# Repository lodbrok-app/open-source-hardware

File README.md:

# open-source-hardware
Open-source components of the Lodbrok stack

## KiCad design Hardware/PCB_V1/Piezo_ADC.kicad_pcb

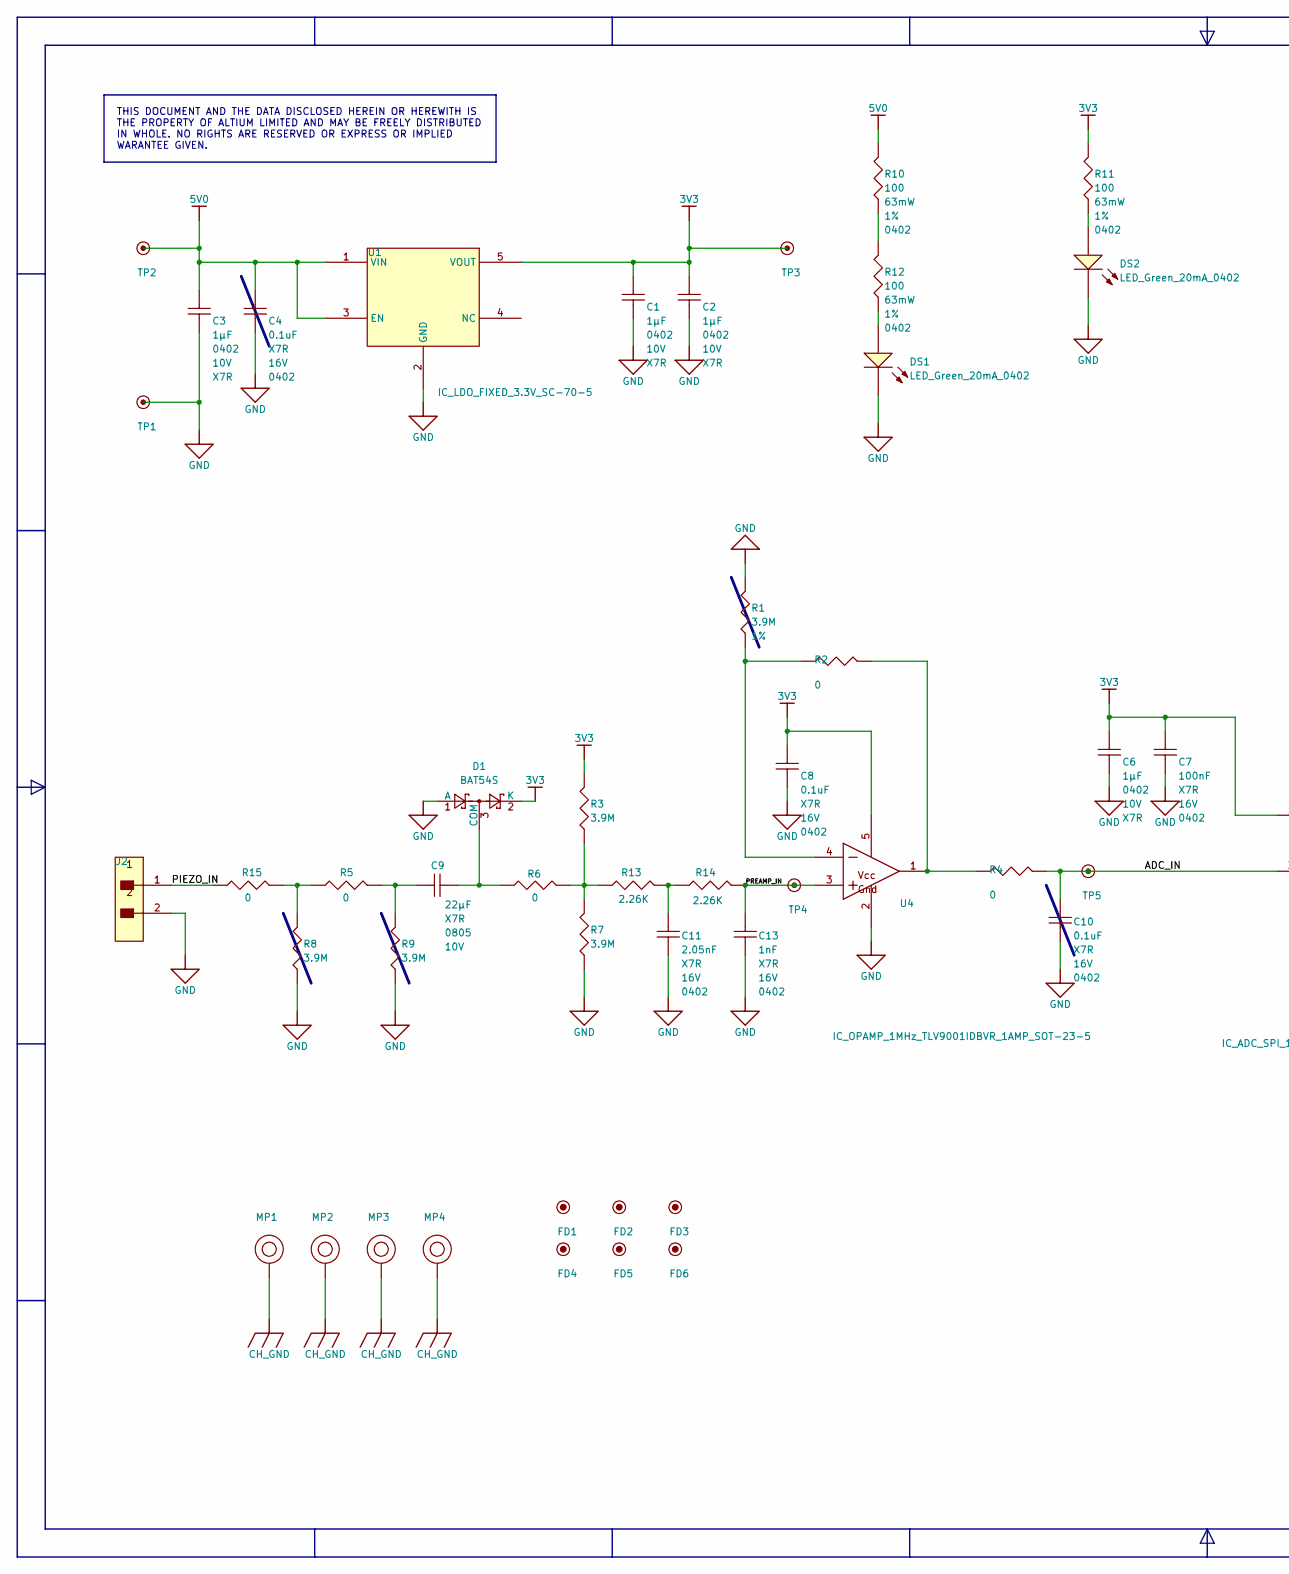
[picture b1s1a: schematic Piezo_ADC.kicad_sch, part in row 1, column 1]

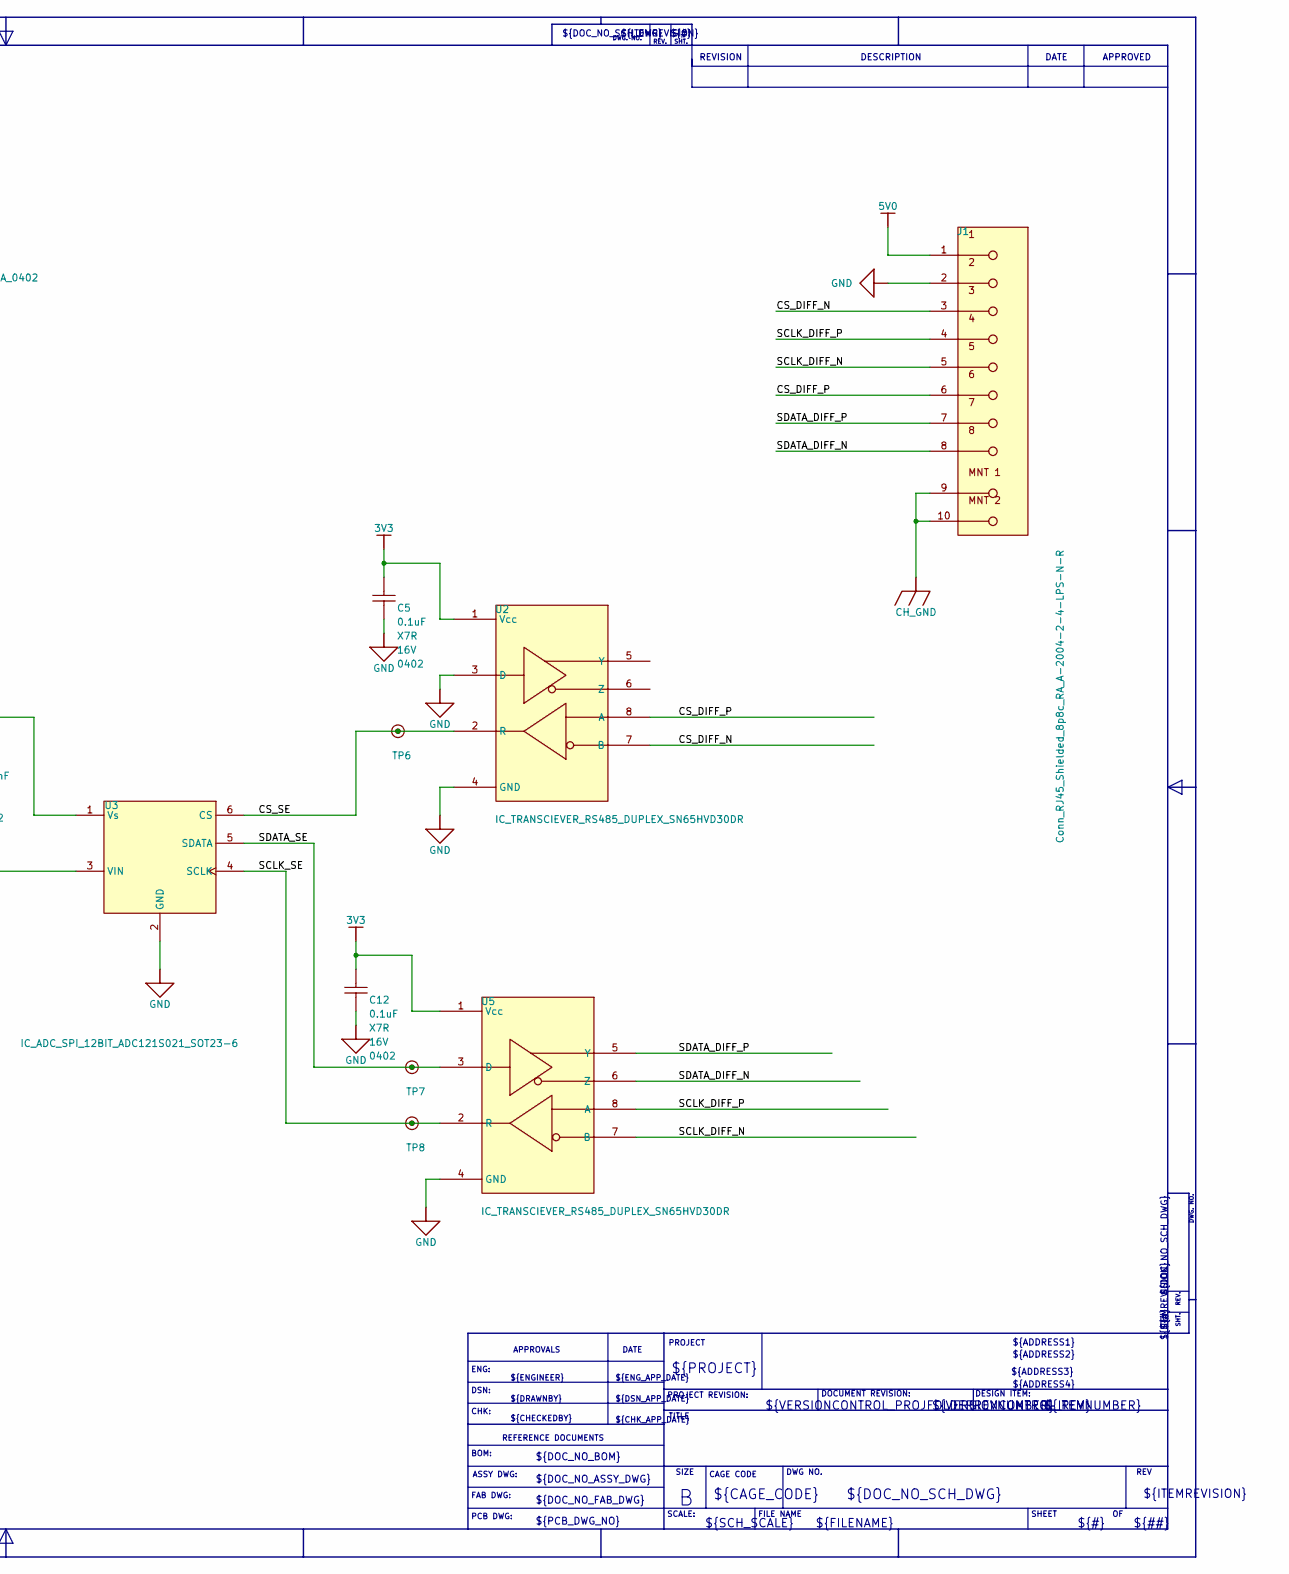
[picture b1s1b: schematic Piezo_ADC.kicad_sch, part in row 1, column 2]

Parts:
C1, C2, C3, C6: Cap_1uF_10%_10V_0402; CAP_0402_0.6mm_Height; VOLTAGE RATING 10V; TOLERANCE 10%
C4, C5, C7, C8, C10, C12: Cap_0.1uF_10%_16V_0402; CAP_0402_0.6mm_Height; TOLERANCE 10%; VOLTAGE RATING 16V
C9: Cap_22uF_20%_10V_0805; CAP_0805_1.45mm_Height; TOLERANCE 20%; VOLTAGE RATING 10V
C11: Cap_2.05nF_10%_16V_0402; CAP_0402_0.6mm_Height; TOLERANCE 10%; VOLTAGE RATING 16V
C13: Cap_1nF_10%_16V_0402; CAP_0402_0.6mm_Height; TOLERANCE 10%; VOLTAGE RATING 16V
D1: BAT54S; SOT-23
DS1, DS2: LED_Green_20mA_0402; LED_0402_Green_KA; FORWARD VOLTAGE 2.1V
FD1, FD2, FD3, FD4, FD5, FD6: FID1X2R
J1: Conn_RJ45_Shielded_8p8c_RA_A-2004-2-4-LPS-N-R; A-2004-2-4-LPS-N-R; VOLTAGE RATING 150V
J2: Conn_2Pos_3.96mm_1Row_TH_JST_B2PS-VH; JST_B2PS-VH-FP; VOLTAGE RATING 250V; MPN1 B2PS-VH
MP1, MP2, MP3, MP4: STAND_OFF_M3_2mm_NS_SMT; 9774020960
R1: Res_3M9_1%_63mW_0402; RES_0402; TOLERANCE 1%; VOLTAGE RATING 50V
R2, R4, R5, R6, R15: Res_0R0_1%_63mW_0402; RES_0402; VOLTAGE RATING 50V
R3, R7, R8, R9: Res_3M9_1%_63mW_0402; RES_0402; VOLTAGE RATING 50V
R10, R11, R12: Res_100R_1%_63mW_0402; RES_0402; TOLERANCE 1%; VOLTAGE RATING 50V
R13, R14: Res_2.26kR0_1%_63mW_0402; RES_0402; VOLTAGE RATING 50V
TP1, TP3, TP5, TP6, TP7, TP8: TPAD6R; Keystone 5001 TP
TP2, TP4: TPAD6R; TP06R
U1: IC_LDO_FIXED_3.3V_SC-70-5; SOT23-5; OUTPUT VOLTAGE 3.3V; DROPOUT VOLTAGE 310mV
U2, U5: IC_TRANSCIEVER_RS485_DUPLEX_SN65HVD30DR; SOIC-8
U3: IC_ADC_SPI_12BIT_ADC121S021_SOT23-6; SOT-23-6
U4: IC_OPAMP_1MHz_TLV9001IDBVR_1AMP_SOT-23-5; SOT23-5; MPN1 TLV9001IDBVR

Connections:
3V3: C1.2, C2.2, C5.2, C6.2, C7.2, C8.2, C12.2, D1.2 (K), R3.2, R11.2, TP3.1 (TP_1), U1.5 (VOUT), U2.1 (Vcc), U3.1 (Vs), U4.5 (Vcc), U5.1 (Vcc)
5V0: C3.2, C4.2, J1.1, R10.2, TP2.1 (TP_1), U1.1 (VIN), U1.3 (EN)
/ADC_IN: C10.1, R4.2, TP5.1 (TP_1), U3.3 (VIN)
/CS_DIFF_N: J1.3, U2.7 (B)
/CS_DIFF_P: J1.6, U2.8 (A)
/CS_SE: TP6.1 (TP_1), U2.2 (R), U3.6 (CS)
/PIEZO_IN: J2.1, R15.1
/PREAMP_IN: C13.1, R14.2, TP4.1 (TP_1), U4.3 (+IN)
/SCLK_DIFF_N: J1.5, U5.7 (B)
/SCLK_DIFF_P: J1.4, U5.8 (A)
/SCLK_SE: TP8.1 (TP_1), U3.4 (SCLK), U5.2 (R)
/SDATA_DIFF_N: J1.8, U5.6 (Z)
/SDATA_DIFF_P: J1.7, U5.5 (Y)
/SDATA_SE: TP7.1 (TP_1), U3.5 (SDATA), U5.3 (D)
CH_GND: J1.9 (MNT_1), J1.10 (MNT_2), MP1.1 (1_1), MP2.1 (1_1), MP3.1 (1_1), MP4.1 (1_1)
GND: C1.1, C2.1, C3.1, C4.1, C5.1, C6.1, C7.1, C8.1, C10.2, C11.2, C12.1, C13.2, D1.1 (A), DS1.2 (K), DS2.2 (K), J1.2, J2.2, R1.2, R7.1, R8.1, R9.1, TP1.1 (TP_1), U1.2 (GND), U2.3 (D), U2.4 (GND), U3.2 (GND), U4.2 (GND), U5.4 (GND)
unnamed: C9.1, R5.2, R9.2
unnamed: C11.1, R13.2, R14.1
unnamed: C9.2, D1.3 (COM), R6.1
unnamed: DS1.1 (A), R12.1
unnamed: DS2.1 (A), R11.1
unnamed: R10.1, R12.2
unnamed: R3.1, R6.2, R7.2, R13.1
unnamed: R5.1, R8.2, R15.2
unnamed: R1.1, R2.1, U4.4 (-IN)
unnamed: R2.2, R4.1, U4.1 (OUT)

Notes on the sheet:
DESCRIPTION
${DOC_NO_SCH_DWG}
${CHK_APP_DATE}
SHT.
APPROVED
PCB DWG:
PROJECT
${#}
DWG NO.
REV
${VERSIONCONTROL_PROJFOLDERREVNUMBER}
${ADDRESS1}
FILE NAME
${ITEMREVISION}
DWG. NO.
${ENGINEER}
DESIGN ITEM:
REFERENCE DOCUMENTS
DATE
REV.
${##}
ENG:
APPROVALS
${CHECKEDBY}
${CAGE_CODE}
FAB DWG:
TITLE
SHEET
${DOC_NO_FAB_DWG}
SCALE:
${DSN_APP_DATE}
CHK:
${VERSIONCONTROL_REVNUMBER}
${TITLE}
SIZE
${PROJECT}
DSN:
PROJECT REVISION:
${PCB_DWG_NO}
CAGE CODE

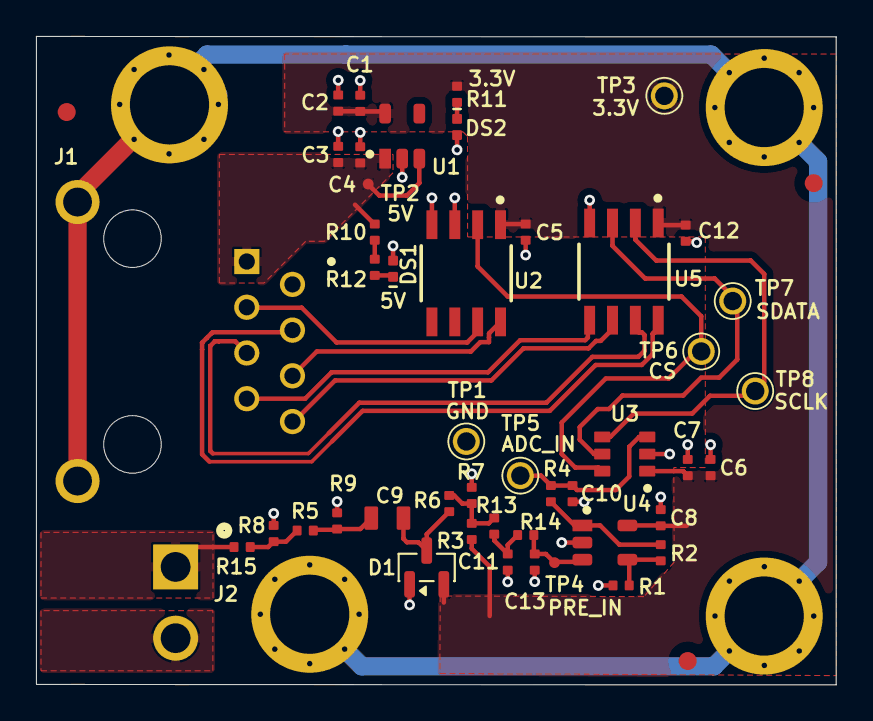
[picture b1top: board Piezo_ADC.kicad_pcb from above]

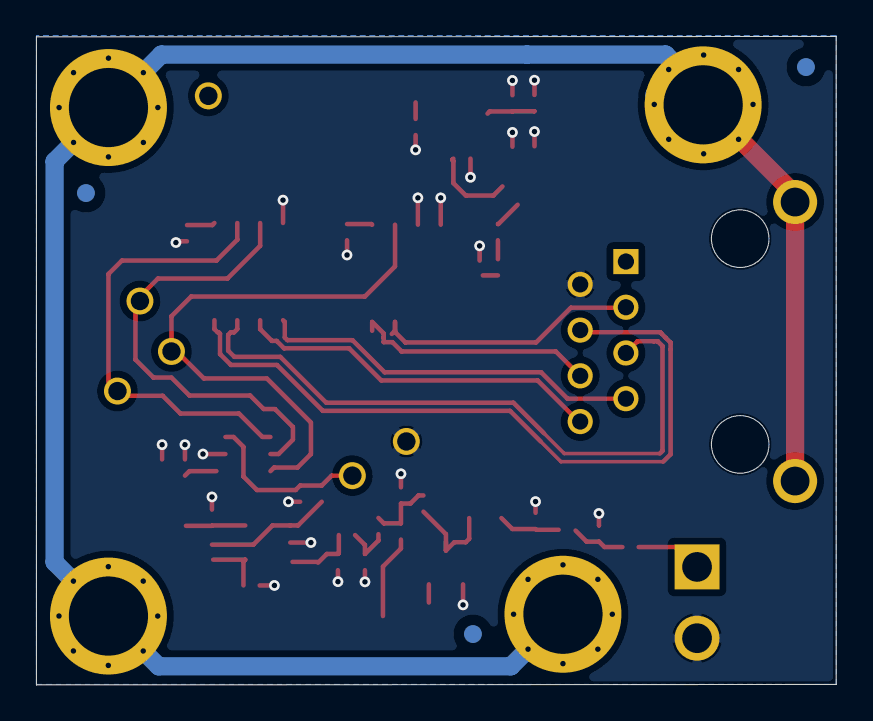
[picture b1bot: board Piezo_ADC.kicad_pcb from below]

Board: 2 copper layers, 44.4 x 36.0 mm, 56 parts (7 on the bottom side), 26 nets.

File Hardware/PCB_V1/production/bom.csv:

Designator,Footprint,Quantity,Value,LCSC Part #
"C1, C2, C3, C6",CAP_0402_0.6mm_Height,4,Cap_1uF_10%_10V_0402,
"C10, C12, C4, C5, C7, C8",CAP_0402_0.6mm_Height,6,Cap_0.1uF_10%_16V_0402,
C11,CAP_0402_0.6mm_Height,1,Cap_2.05nF_10%_16V_0402,
C13,CAP_0402_0.6mm_Height,1,Cap_1nF_10%_16V_0402,
C9,CAP_0805_1.45mm_Height,1,Cap_22uF_20%_10V_0805,
D1,SOT-23,1,BAT54S,
"DS1, DS2",LED_0402_Green_KA,2,LED_Green_20mA_0402,
"FD1, FD2, FD3, FD4, FD5, FD6",FID1X2R,6,FID1X2R,
J1,A-2004-2-4-LPS-N-R,1,Conn_RJ45_Shielded_8p8c_RA_A-2004-2-4-LPS-N-R,
J2,JST_B2PS-VH-FP,1,Conn_2Pos_3.96mm_1Row_TH_JST_B2PS-VH,
"MP1, MP2, MP3, MP4",9774020960,4,STAND_OFF_M3_2mm_NS_SMT,
"R1, R3, R7, R8, R9",RES_0402,5,Res_3M9_1%_63mW_0402,
"R10, R11, R12",RES_0402,3,Res_100R_1%_63mW_0402,
"R13, R14",RES_0402,2,Res_2.26kR0_1%_63mW_0402,
"R15, R2, R4, R5, R6",RES_0402,5,Res_0R0_1%_63mW_0402,
"TP1, TP3, TP5, TP6, TP7, TP8",Keystone 5001 TP,6,TPAD6R,
"TP2, TP4",TP06R,2,TPAD6R,
U1,SOT23-5,1,IC_LDO_FIXED_3.3V_SC-70-5,
"U2, U5",SOIC-8,2,IC_TRANSCIEVER_RS485_DUPLEX_SN65HVD30DR,
U3,SOT-23-6,1,IC_ADC_SPI_12BIT_ADC121S021_SOT23-6,
U4,SOT23-5,1,IC_OPAMP_1MHz_TLV9001IDBVR_1AMP_SOT-23-5,
